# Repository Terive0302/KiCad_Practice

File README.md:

# KiCad_Practice

[유튜브 강의](https://www.youtube.com/watch?v=MrIUESCI15k&list=PLj5NnUk28LOecGFEXqgYY5xdjfHh7dqTh)를 참고하여 KiCad(카이캐드)실습   
<br>
강의는 총 15편으로 이루어져 있으며 마지막에는 PCB기판을 주문하는 것을 목적으로 하는 **공부**를 진행.   
***
### Exam PCB Img

<br><br>
### Exam 3D Front Img

<br><br>
### Exam 3D Back Img

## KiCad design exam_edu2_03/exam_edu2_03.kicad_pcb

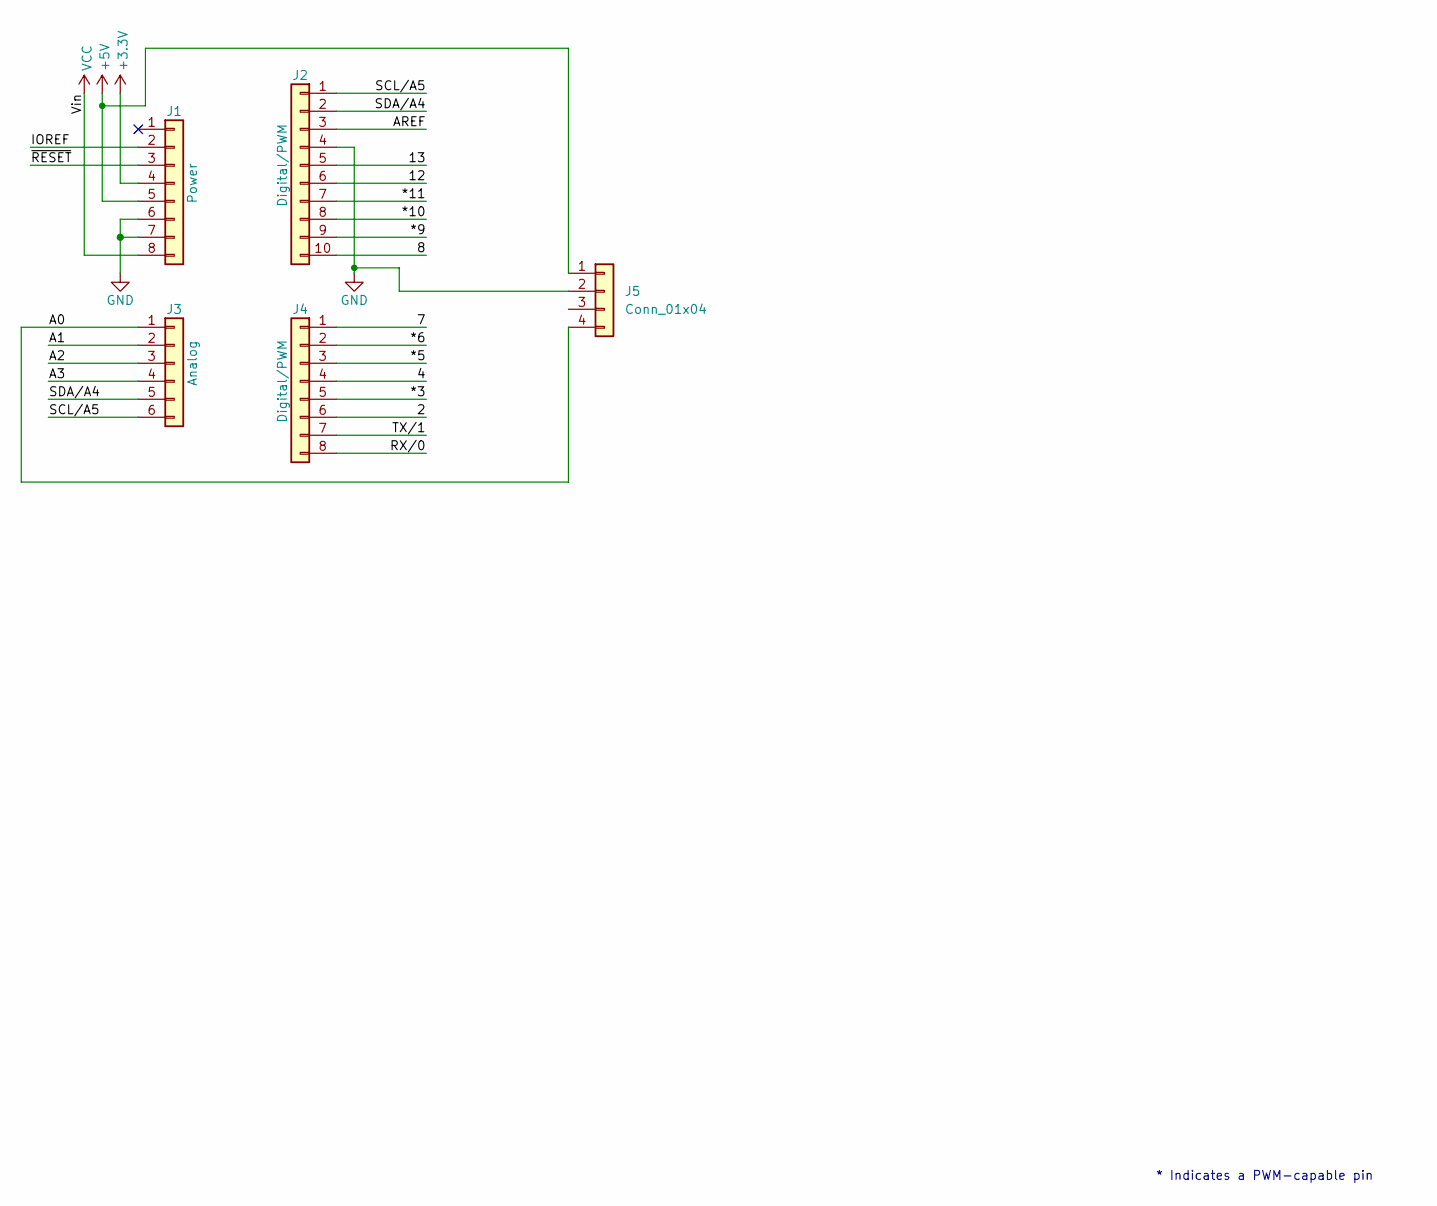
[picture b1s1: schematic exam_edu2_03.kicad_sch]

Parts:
J1: Power; PinSocket_1x08_P2.54mm_Vertical
J2: Digital/PWM; PinSocket_1x10_P2.54mm_Vertical
J3: Analog; PinSocket_1x06_P2.54mm_Vertical
J4: Digital/PWM; PinSocket_1x08_P2.54mm_Vertical
J5: Conn_01x04; PinSocket_1x04_P2.54mm_Vertical

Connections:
+3V3: J1.4
+5V: J1.5, J5.1
/2: J4.6
/4: J4.4
/7: J4.1
/8: J2.10
/12: J2.6
/13: J2.5
/*3: J4.5
/*5: J4.3
/*6: J4.2
/*9: J2.9
/*10: J2.8
/*11: J2.7
/A0: J3.1, J5.4
/A1: J3.2
/A2: J3.3
/A3: J3.4
/AREF: J2.3
/IOREF: J1.2
/RX/0: J4.8
/SCL/A5: J2.1, J3.6
/SDA/A4: J2.2, J3.5
/TX/1: J4.7
/~RESET: J1.3
GND: J1.6, J1.7, J2.4, J5.2
VCC: J1.8

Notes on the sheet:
* Indicates a PWM-capable pin

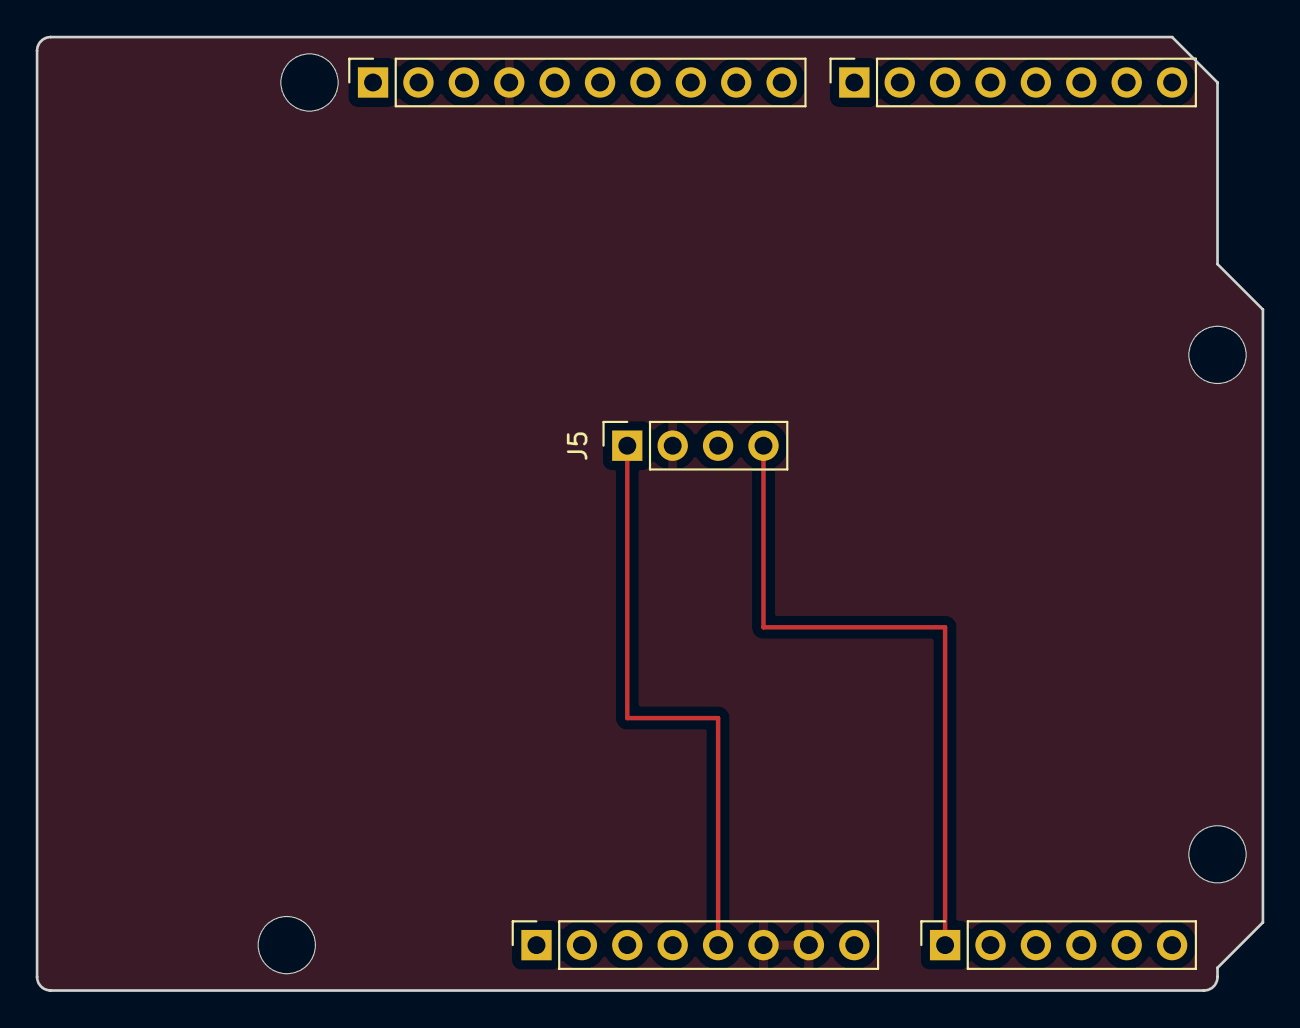
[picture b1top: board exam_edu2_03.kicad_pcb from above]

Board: 2 copper layers, 68.6 x 53.3 mm, 9 parts (0 on the bottom side), 5 nets.

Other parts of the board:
MH1, MH2, MH3, MH4: MountingHole_3.2mm

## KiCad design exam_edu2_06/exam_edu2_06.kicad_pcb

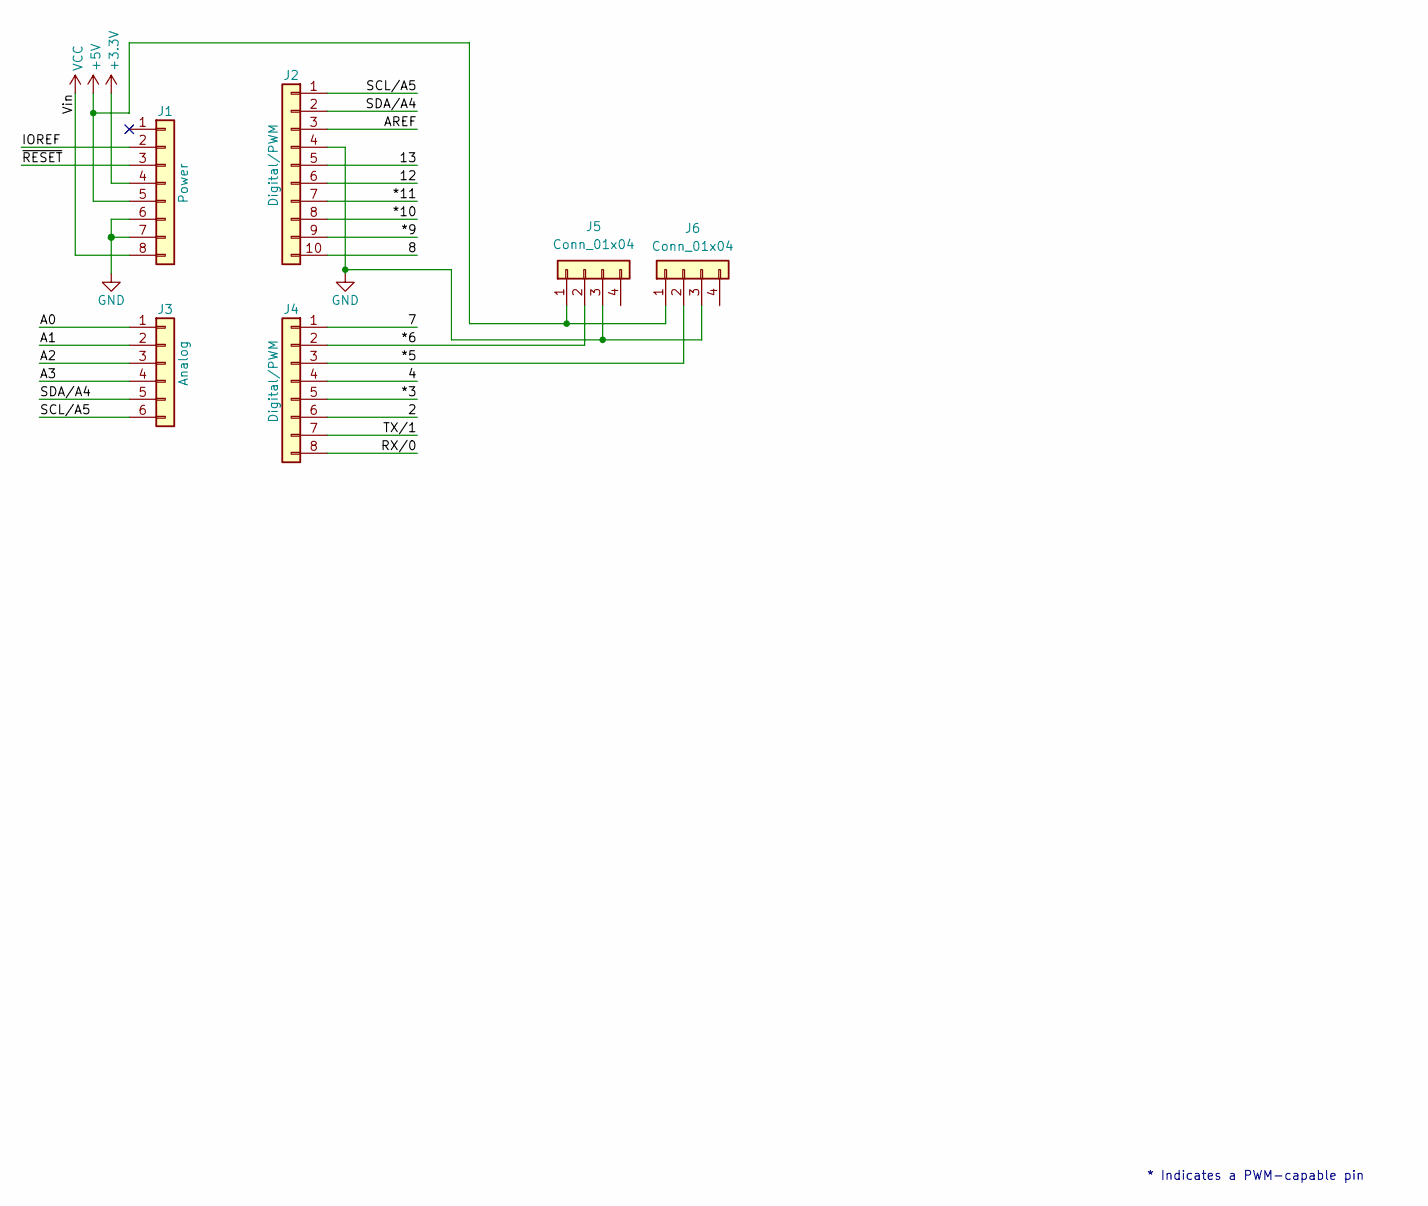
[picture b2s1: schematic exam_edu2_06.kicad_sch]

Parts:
J1: Power; PinSocket_1x08_P2.54mm_Vertical
J2: Digital/PWM; PinSocket_1x10_P2.54mm_Vertical
J3: Analog; PinSocket_1x06_P2.54mm_Vertical
J4: Digital/PWM; PinSocket_1x08_P2.54mm_Vertical
J5, J6: Conn_01x04; JST_XH_S4B-XH-A-1_1x04_P2.50mm_Horizontal

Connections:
+3V3: J1.4
+5V: J1.5, J5.1, J6.1
/2: J4.6
/4: J4.4
/7: J4.1
/8: J2.10
/12: J2.6
/13: J2.5
/*3: J4.5
/*5: J4.3, J6.2
/*6: J4.2, J5.2
/*9: J2.9
/*10: J2.8
/*11: J2.7
/A0: J3.1
/A1: J3.2
/A2: J3.3
/A3: J3.4
/AREF: J2.3
/IOREF: J1.2
/RX/0: J4.8
/SCL/A5: J2.1, J3.6
/SDA/A4: J2.2, J3.5
/TX/1: J4.7
/~RESET: J1.3
GND: J1.6, J1.7, J2.4, J5.3, J6.3
VCC: J1.8

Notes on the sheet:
* Indicates a PWM-capable pin

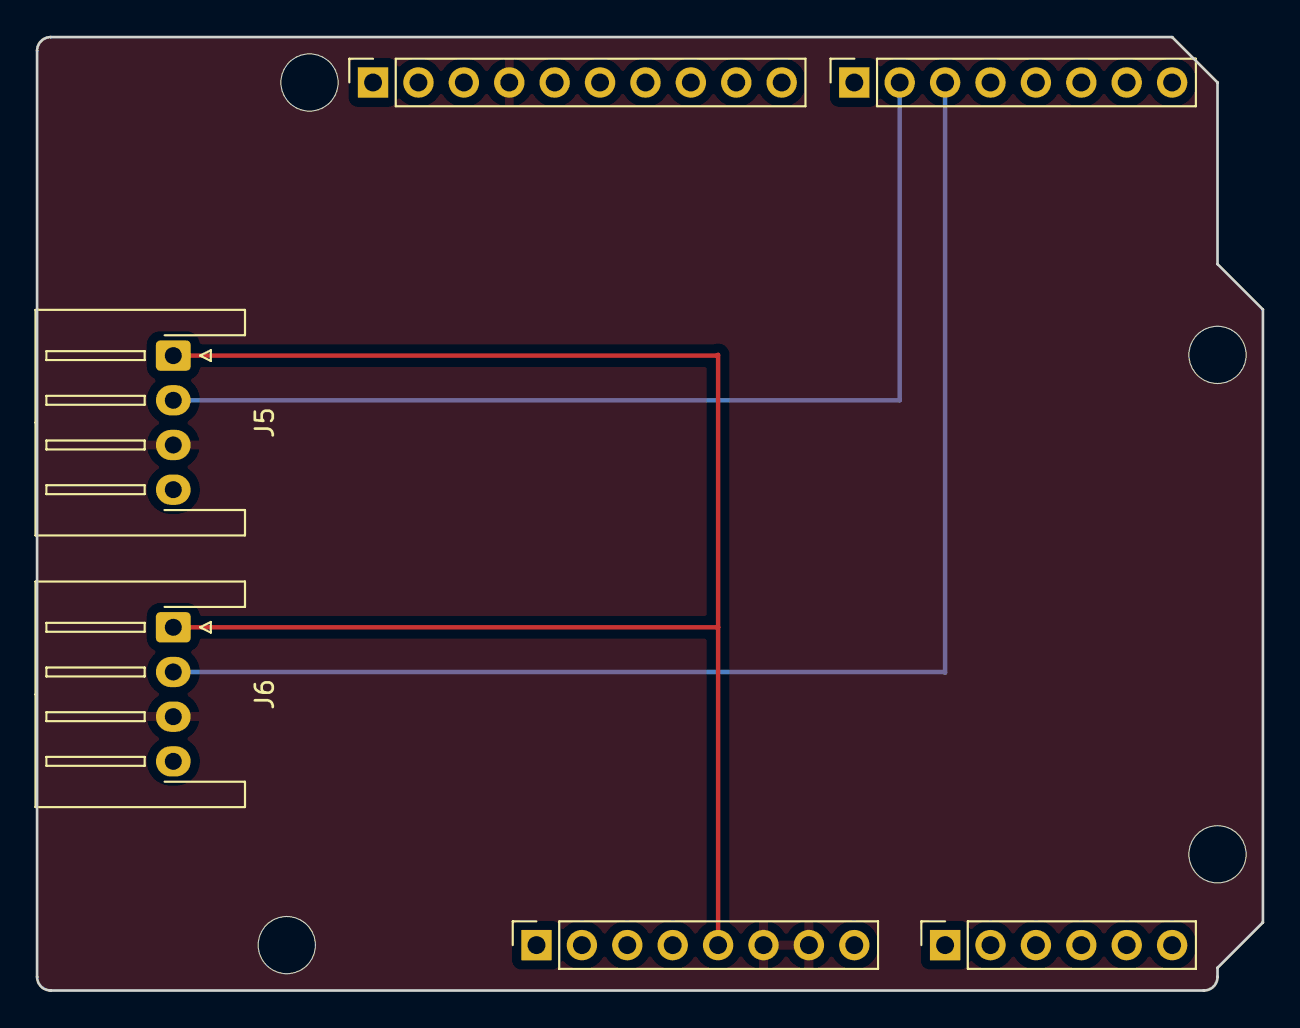
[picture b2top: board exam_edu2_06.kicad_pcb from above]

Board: 2 copper layers, 68.6 x 53.3 mm, 10 parts (0 on the bottom side), 6 nets.

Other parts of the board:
MH1, MH2, MH3, MH4: MountingHole_3.2mm

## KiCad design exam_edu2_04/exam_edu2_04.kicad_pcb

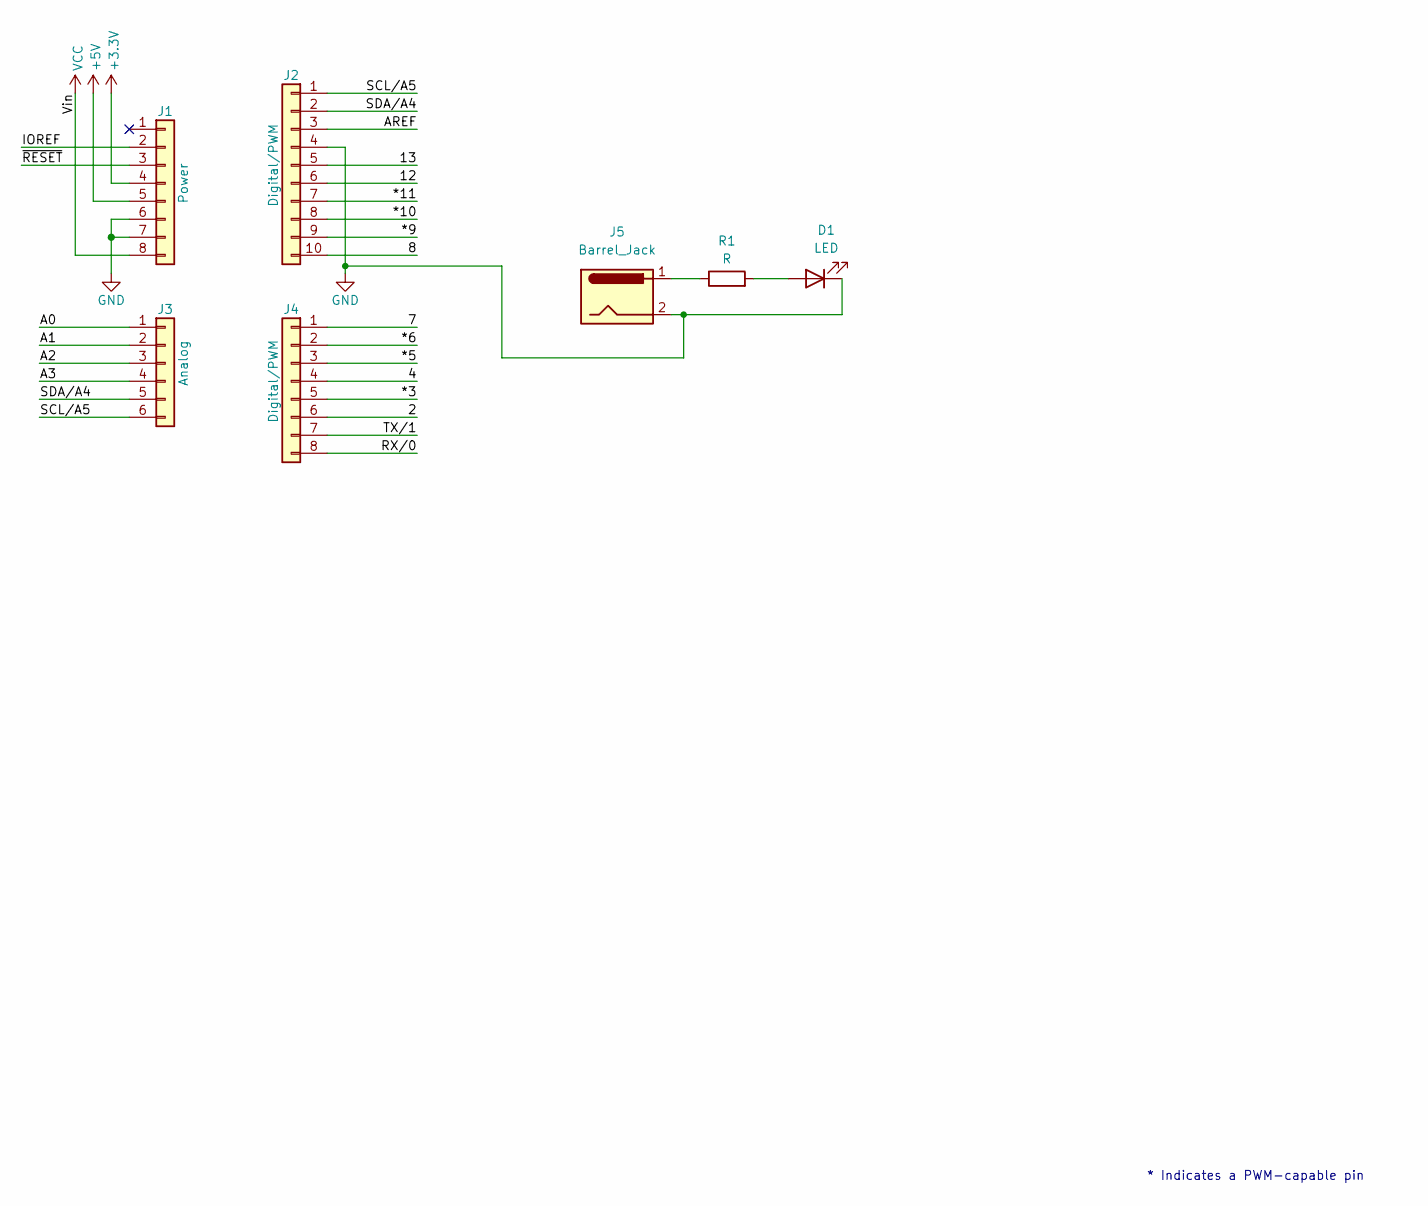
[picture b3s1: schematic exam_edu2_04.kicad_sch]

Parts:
D1: LED; LED_D3.0mm
J1: Power; PinSocket_1x08_P2.54mm_Vertical
J2: Digital/PWM; PinSocket_1x10_P2.54mm_Vertical
J3: Analog; PinSocket_1x06_P2.54mm_Vertical
J4: Digital/PWM; PinSocket_1x08_P2.54mm_Vertical
J5: Barrel_Jack; BarrelJack_Horizontal
R1: R; R_Axial_DIN0204_L3.6mm_D1.6mm_P7.62mm_Horizontal

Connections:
+3V3: J1.4
+5V: J1.5
/2: J4.6
/4: J4.4
/7: J4.1
/8: J2.10
/12: J2.6
/13: J2.5
/*3: J4.5
/*5: J4.3
/*6: J4.2
/*9: J2.9
/*10: J2.8
/*11: J2.7
/A0: J3.1
/A1: J3.2
/A2: J3.3
/A3: J3.4
/AREF: J2.3
/IOREF: J1.2
/RX/0: J4.8
/SCL/A5: J2.1, J3.6
/SDA/A4: J2.2, J3.5
/TX/1: J4.7
/~RESET: J1.3
GND: D1.1 (K), J1.6, J1.7, J2.4, J5.2
unnamed: D1.2 (A), R1.2
unnamed: J5.1, R1.1
VCC: J1.8

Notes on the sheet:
* Indicates a PWM-capable pin

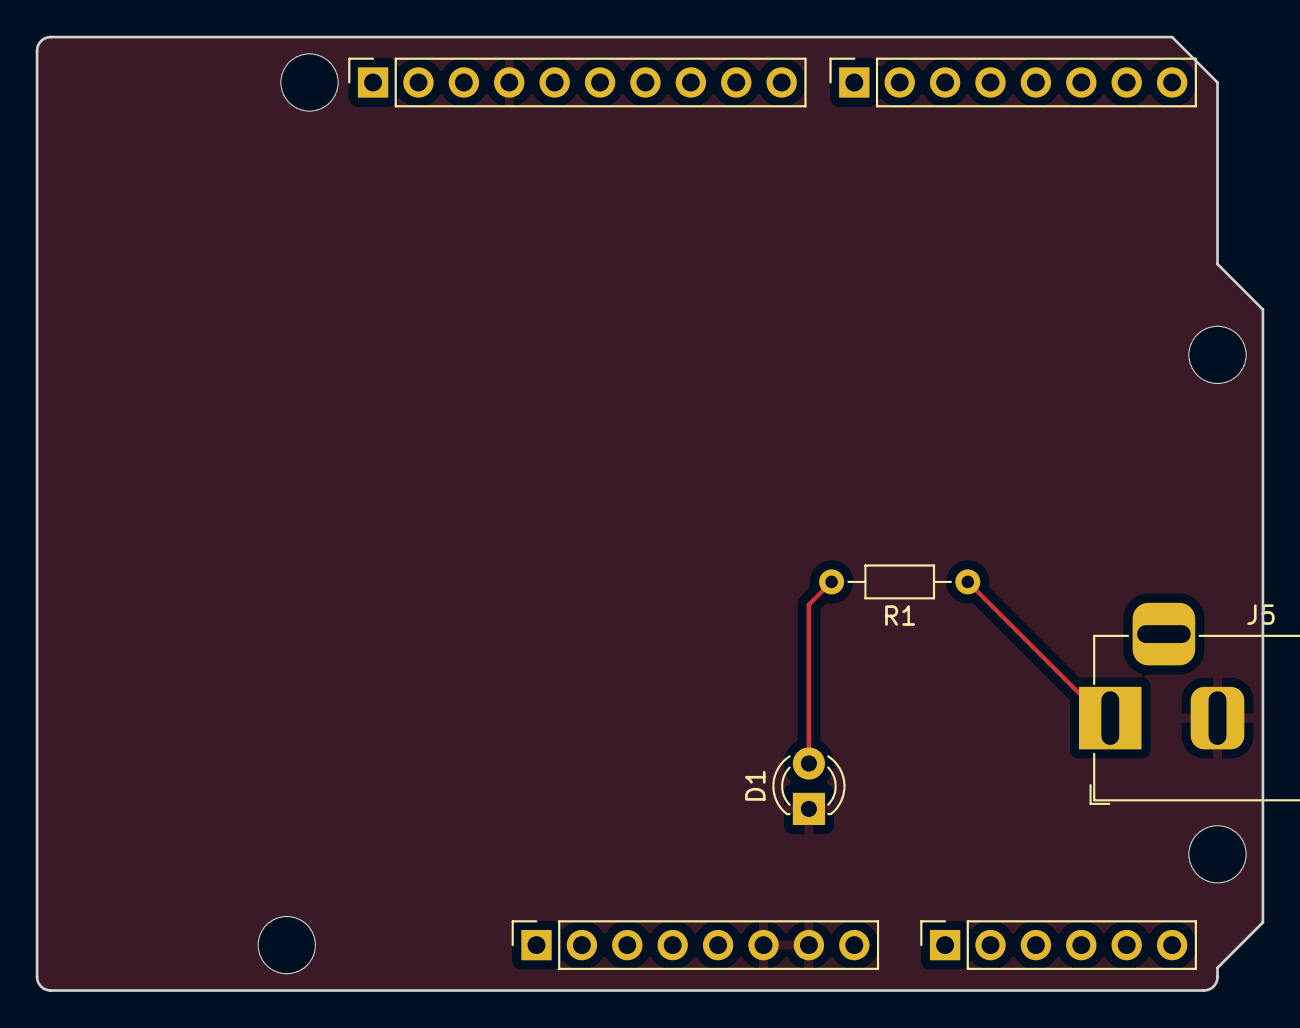
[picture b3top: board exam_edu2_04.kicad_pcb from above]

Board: 2 copper layers, 68.6 x 53.3 mm, 11 parts (0 on the bottom side), 5 nets.

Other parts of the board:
MH1, MH2, MH3, MH4: MountingHole_3.2mm

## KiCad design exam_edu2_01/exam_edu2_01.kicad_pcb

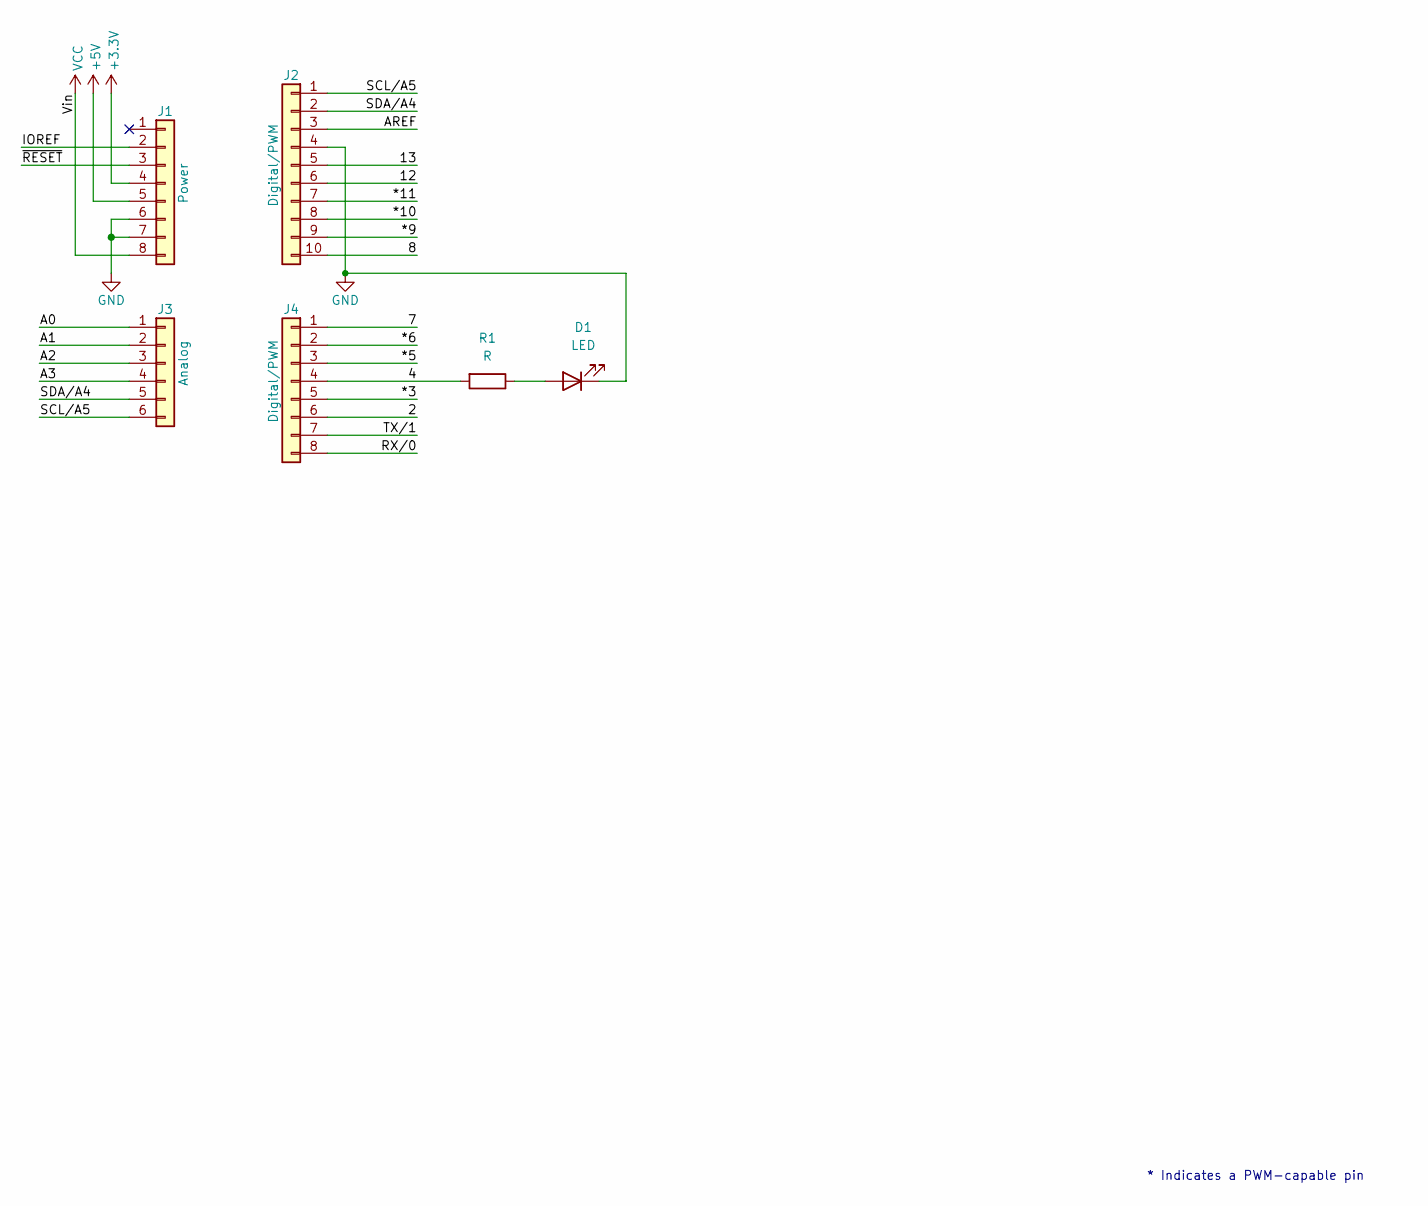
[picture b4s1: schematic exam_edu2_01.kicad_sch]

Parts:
D1: LED; LED_D4.0mm
J1: Power; PinSocket_1x08_P2.54mm_Vertical
J2: Digital/PWM; PinSocket_1x10_P2.54mm_Vertical
J3: Analog; PinSocket_1x06_P2.54mm_Vertical
J4: Digital/PWM; PinSocket_1x08_P2.54mm_Vertical
R1: R; R_Axial_DIN0204_L3.6mm_D1.6mm_P7.62mm_Horizontal

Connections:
+3V3: J1.4
+5V: J1.5
/2: J4.6
/4: J4.4, R1.2
/7: J4.1
/8: J2.10
/12: J2.6
/13: J2.5
/*3: J4.5
/*5: J4.3
/*6: J4.2
/*9: J2.9
/*10: J2.8
/*11: J2.7
/A0: J3.1
/A1: J3.2
/A2: J3.3
/A3: J3.4
/AREF: J2.3
/IOREF: J1.2
/RX/0: J4.8
/SCL/A5: J2.1, J3.6
/SDA/A4: J2.2, J3.5
/TX/1: J4.7
/~RESET: J1.3
GND: D1.1 (K), J1.6, J1.7, J2.4
unnamed: D1.2 (A), R1.1
VCC: J1.8

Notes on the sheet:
* Indicates a PWM-capable pin

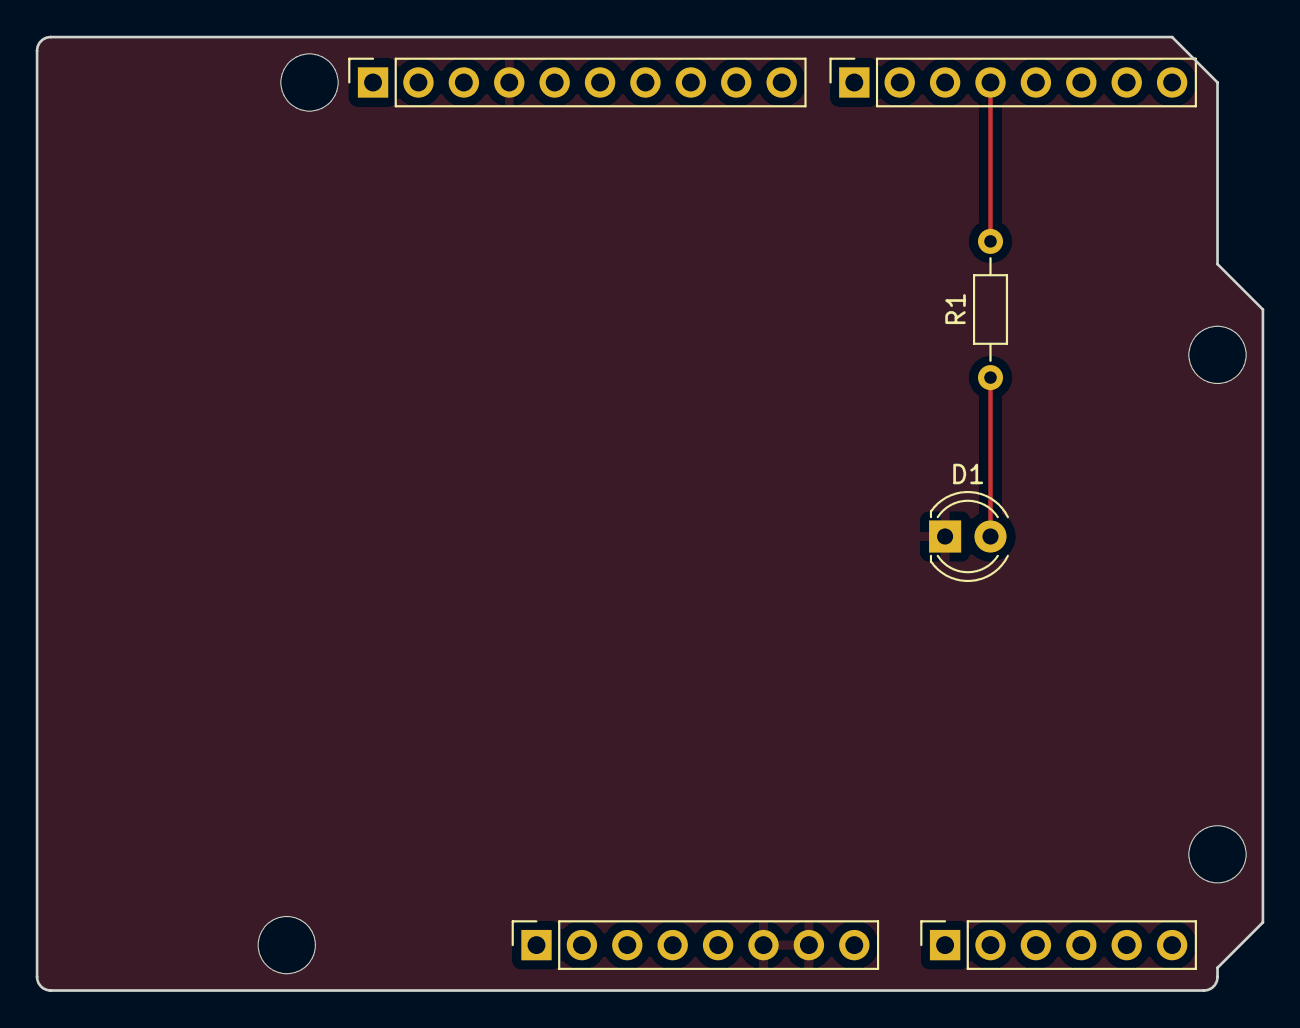
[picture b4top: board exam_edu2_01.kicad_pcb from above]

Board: 2 copper layers, 68.6 x 53.3 mm, 10 parts (0 on the bottom side), 5 nets.

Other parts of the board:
MH1, MH2, MH3, MH4: MountingHole_3.2mm

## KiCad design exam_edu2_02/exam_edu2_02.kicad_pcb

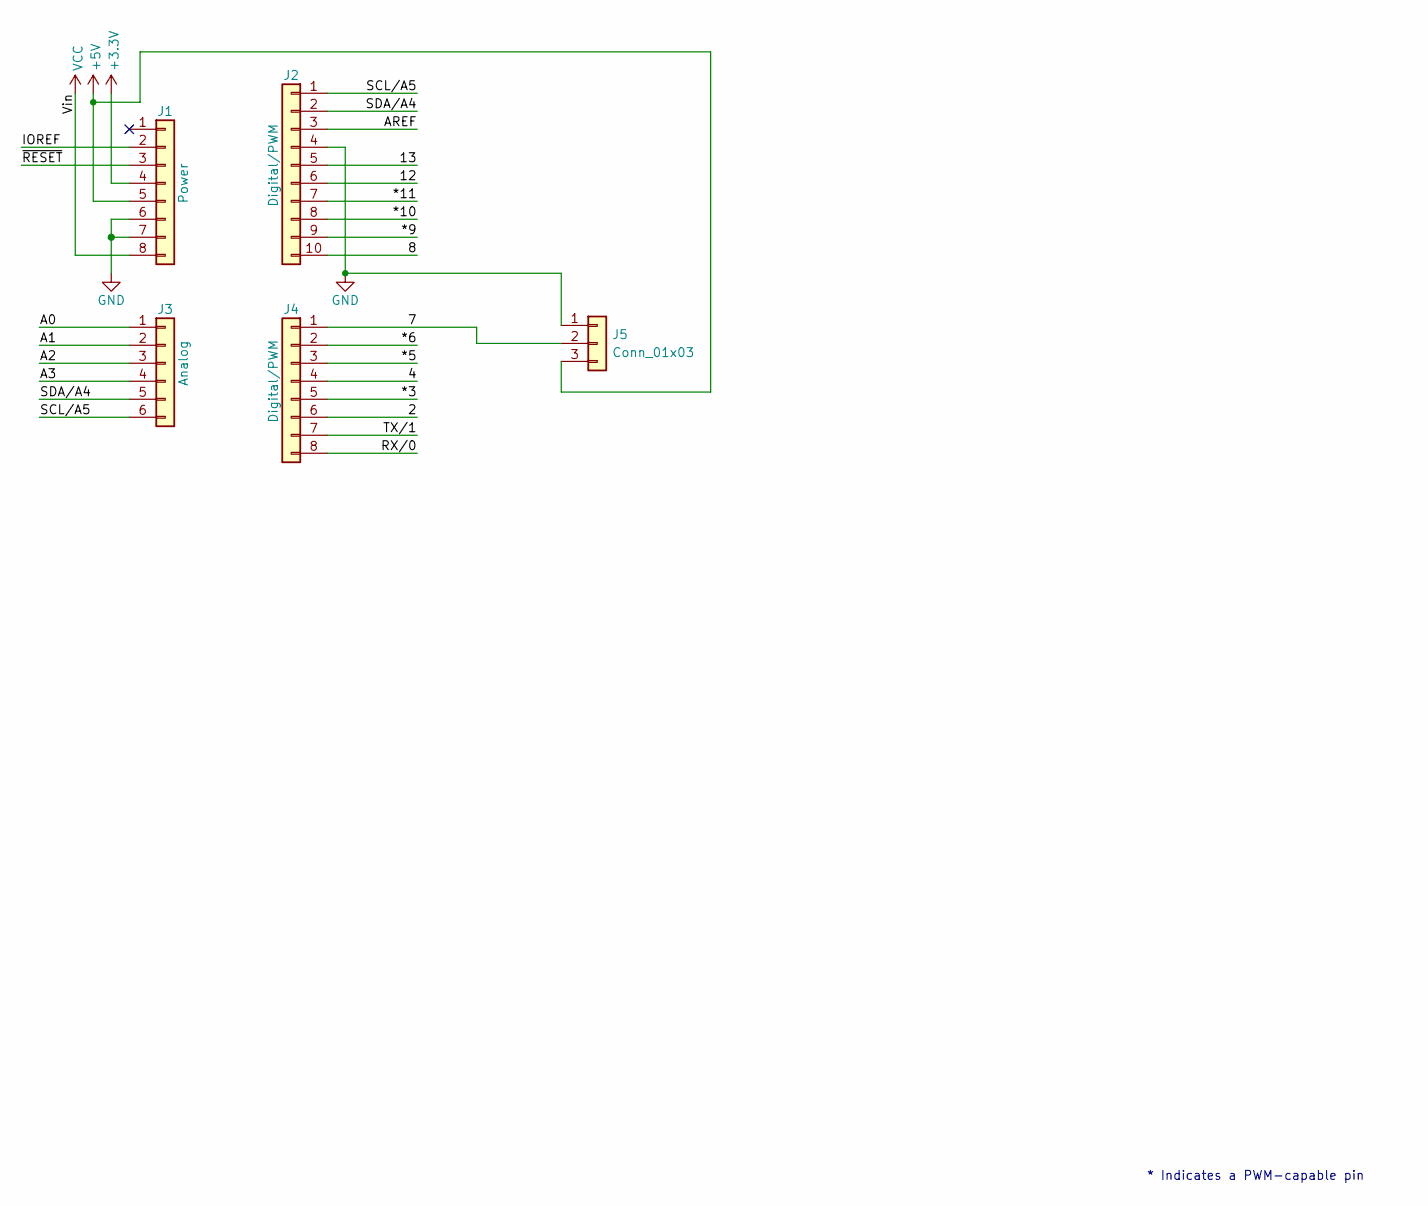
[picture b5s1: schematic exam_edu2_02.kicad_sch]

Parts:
J1: Power; PinSocket_1x08_P2.54mm_Vertical
J2: Digital/PWM; PinSocket_1x10_P2.54mm_Vertical
J3: Analog; PinSocket_1x06_P2.54mm_Vertical
J4: Digital/PWM; PinSocket_1x08_P2.54mm_Vertical
J5: Conn_01x03; PinSocket_1x03_P2.54mm_Vertical

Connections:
+3V3: J1.4
+5V: J1.5, J5.3
/2: J4.6
/4: J4.4
/7: J4.1, J5.2
/8: J2.10
/12: J2.6
/13: J2.5
/*3: J4.5
/*5: J4.3
/*6: J4.2
/*9: J2.9
/*10: J2.8
/*11: J2.7
/A0: J3.1
/A1: J3.2
/A2: J3.3
/A3: J3.4
/AREF: J2.3
/IOREF: J1.2
/RX/0: J4.8
/SCL/A5: J2.1, J3.6
/SDA/A4: J2.2, J3.5
/TX/1: J4.7
/~RESET: J1.3
GND: J1.6, J1.7, J2.4, J5.1
VCC: J1.8

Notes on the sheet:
* Indicates a PWM-capable pin

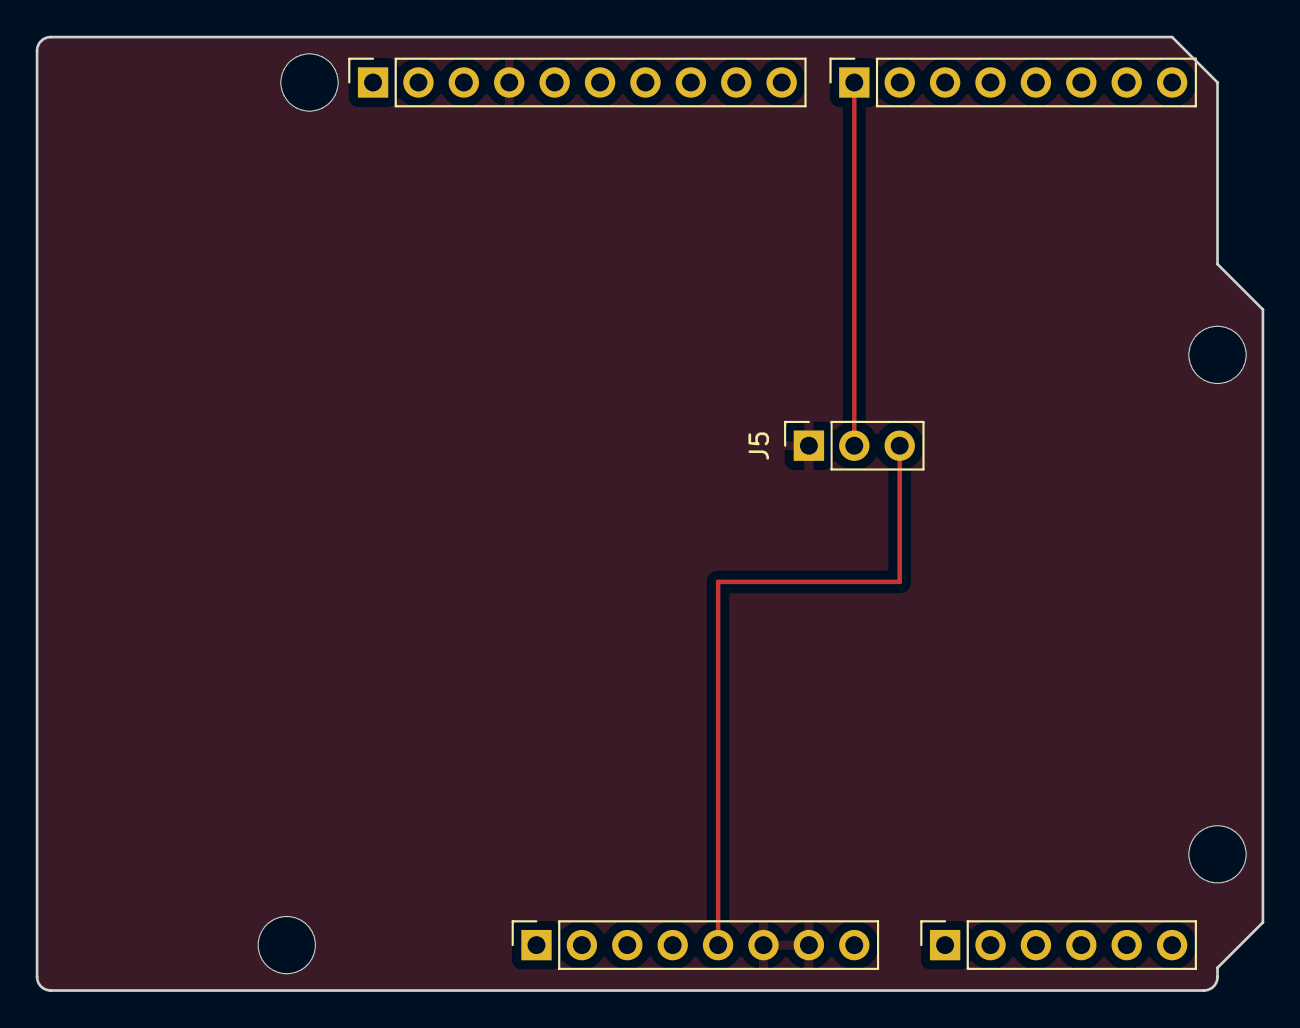
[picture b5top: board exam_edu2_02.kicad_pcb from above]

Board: 2 copper layers, 68.6 x 53.3 mm, 9 parts (0 on the bottom side), 5 nets.

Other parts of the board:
MH1, MH2, MH3, MH4: MountingHole_3.2mm

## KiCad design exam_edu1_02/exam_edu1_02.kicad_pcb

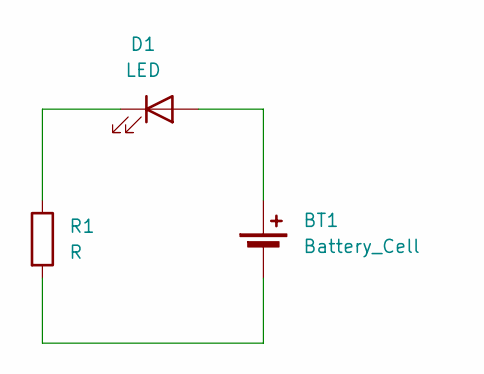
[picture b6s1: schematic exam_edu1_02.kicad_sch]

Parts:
BT1: Battery_Cell; PinSocket_1x02_P2.54mm_Vertical
D1: LED; LED_D3.0mm
R1: R; R_Axial_DIN0204_L3.6mm_D1.6mm_P7.62mm_Horizontal

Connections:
unnamed: BT1.1 (+), D1.2 (A)
unnamed: BT1.2 (-), R1.2
unnamed: D1.1 (K), R1.1

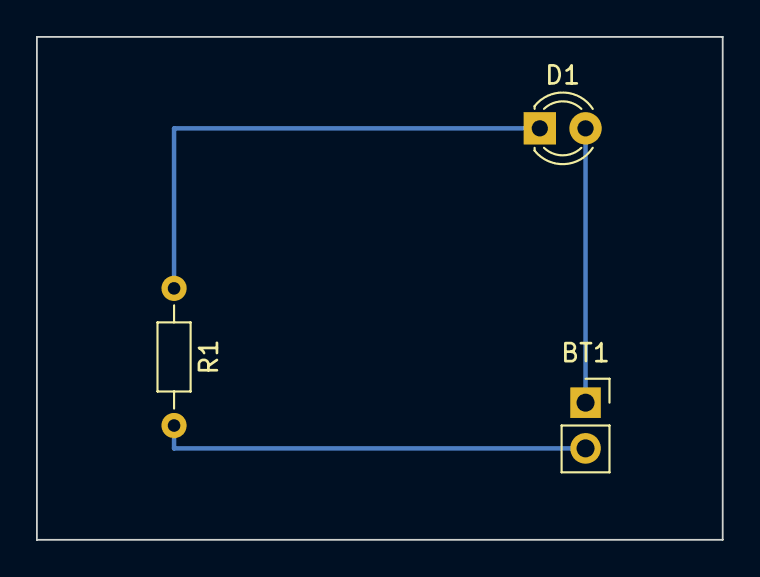
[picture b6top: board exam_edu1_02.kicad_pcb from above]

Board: 2 copper layers, 38.1 x 27.9 mm, 3 parts (0 on the bottom side), 3 nets.

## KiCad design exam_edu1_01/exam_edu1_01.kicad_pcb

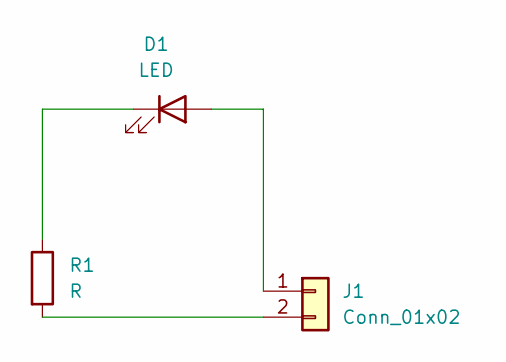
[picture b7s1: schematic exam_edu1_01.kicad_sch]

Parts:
D1: LED; LED_D3.0mm
J1: Conn_01x02; PinSocket_1x02_P2.54mm_Vertical
R1: R; R_Axial_DIN0204_L3.6mm_D1.6mm_P7.62mm_Horizontal

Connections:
unnamed: D1.2 (A), J1.1
unnamed: D1.1 (K), R1.1
unnamed: J1.2, R1.2

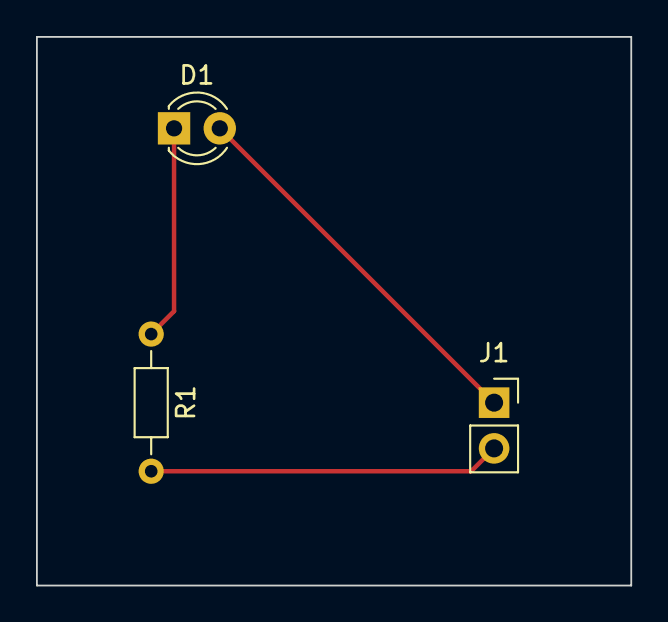
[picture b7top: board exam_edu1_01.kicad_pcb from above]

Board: 2 copper layers, 33.0 x 30.5 mm, 3 parts (0 on the bottom side), 3 nets.

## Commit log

2024-02-07 [Day01] KiCad exam
2024-02-07 [Day02] KiCad exam Temporary
2024-02-07 Rename Day1_2번 결과물 PCB도면.png to Day1_2번_결과물_PCB도면.png
